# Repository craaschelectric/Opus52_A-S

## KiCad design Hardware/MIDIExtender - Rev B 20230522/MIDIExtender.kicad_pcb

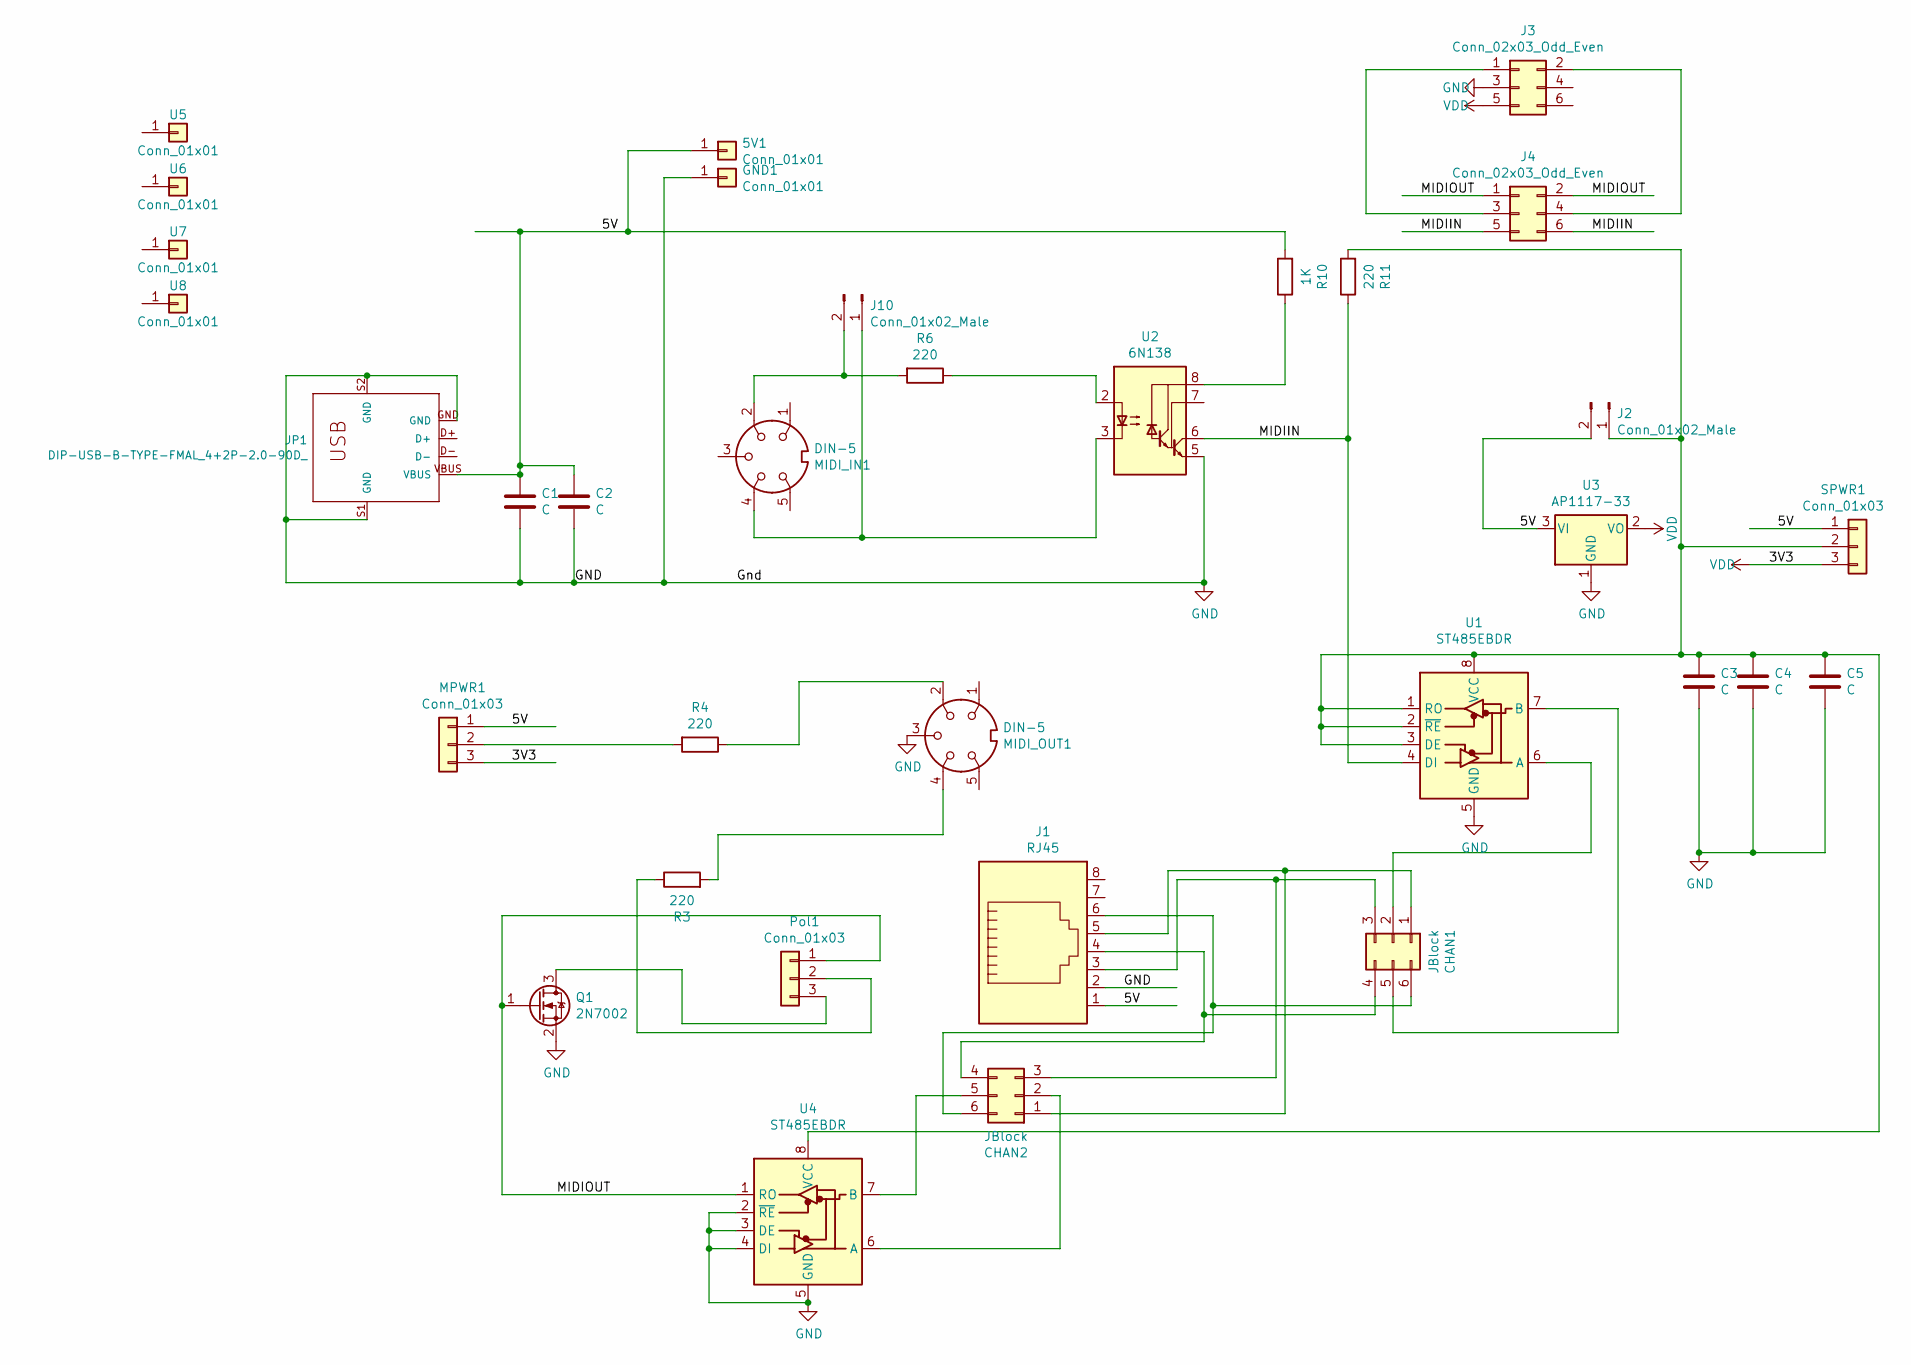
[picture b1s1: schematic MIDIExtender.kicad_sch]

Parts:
5V1: Conn_01x01; KK156-1
C1, C2, C3, C4, C5: C; C_0805_2012Metric_Pad1.15x1.40mm_HandSolder
CHAN1, CHAN2: JBlock; H2X3-2.54
GND1: Conn_01x01; KK156-1
J1: RJ45; RJ45_Amphenol_54602-x08_Horizontal
J2, J10: Conn_01x02_Male; H2-2.54
J3: Conn_02x03_Odd_Even; RibbonCableSocket_6_OddEven
J4: Conn_02x03_Odd_Even; PinHeader_2x03_P2.54mm_Vertical
JP1: DIP-USB-B-TYPE-FMAL_4+2P-2.0-90D_; USB4+2-2.5-90D-15.8X12MM
MIDI_IN1: DIN-5; DIN5_KCDX-5S-S2
MIDI_OUT1: DIN-5; DIN5_KCDX-5S-S2
MPWR1: Conn_01x03; H3-2.54
Pol1: Conn_01x03; H3-2.54
Q1: 2N7002; SOT-23
R3, R4, R6, R11: 220; R_0805_HandSoldering
R10: 1K; R_0805_HandSoldering
SPWR1: Conn_01x03; H3-2.54
U1, U4: ST485EBDR; SOIC-8_3.9x4.9mm_P1.27mm
U2: 6N138; DIP-8_W7.62mm
U3: AP1117-33; SOT-223-3_TabPin2
U5, U7, U8: Conn_01x01; Mounting#4
U6: Conn_01x01; SOT-223-3_TabPin2

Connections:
/5V: 5V1.1, C1.1, C2.1, J1.1, J2.2, JP1.VBUS, MPWR1.1, R10.2, SPWR1.1, U3.3 (VI)
/MIDIIN: J4.5, J4.6, R11.1, U1.4 (DI), U2.6 (VO2)
/MIDIOUT: J4.1, J4.2, Pol1.1, Q1.1 (G), U4.1 (RO)
GND: C1.2, C2.2, C3.2, C4.2, C5.2, GND1.1, J1.2, J3.3, JP1.GND, JP1.S1 (GND), JP1.S2 (GND), MIDI_OUT1.3, Q1.2 (S), U1.5 (GND), U2.5 (GND), U3.1 (GND), U4.2 (~RE), U4.3 (DE), U4.4 (DI), U4.5 (GND)
unnamed: C3.1, C4.1, C5.1, J2.1, R11.2, SPWR1.2, U1.1 (RO), U1.2 (~RE), U1.3 (DE), U1.8 (VCC), U4.8 (VCC)
unnamed: CHAN1.1, CHAN2.1, J1.5
unnamed: CHAN1.2, U1.6 (A)
unnamed: CHAN1.3, CHAN2.3, J1.3
unnamed: CHAN1.4, CHAN2.4, J1.4
unnamed: CHAN1.5, U1.7 (B)
unnamed: CHAN1.6, CHAN2.6, J1.6
unnamed: CHAN2.2, U4.6 (A)
unnamed: CHAN2.5, U4.7 (B)
unnamed: J3.1, J4.3
unnamed: J3.2, J4.4
unnamed: J10.1, MIDI_IN1.4, U2.3 (C2)
unnamed: J10.2, MIDI_IN1.2, R6.2
unnamed: MIDI_OUT1.2, R4.1
unnamed: MIDI_OUT1.4, R3.2
unnamed: MPWR1.2, R4.2
unnamed: Pol1.2, R3.1
unnamed: Pol1.3, Q1.3 (D)
unnamed: R6.1, U2.2 (C1)
unnamed: R10.1, U2.8 (VCC)
VDD: J3.5, MPWR1.3, SPWR1.3, U3.2 (VO)

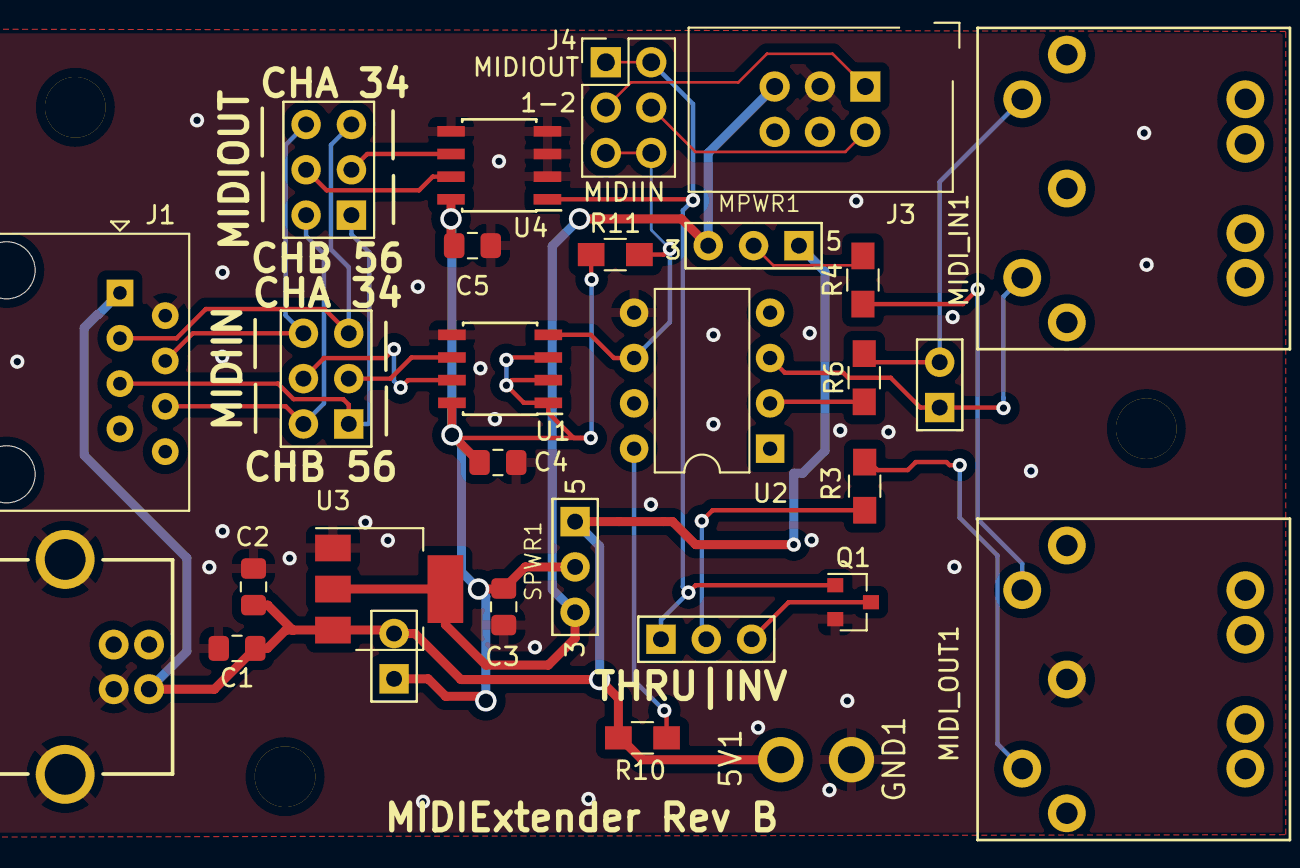
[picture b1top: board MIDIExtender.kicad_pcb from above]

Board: 2 copper layers, 33 parts (0 on the bottom side), 25 nets.

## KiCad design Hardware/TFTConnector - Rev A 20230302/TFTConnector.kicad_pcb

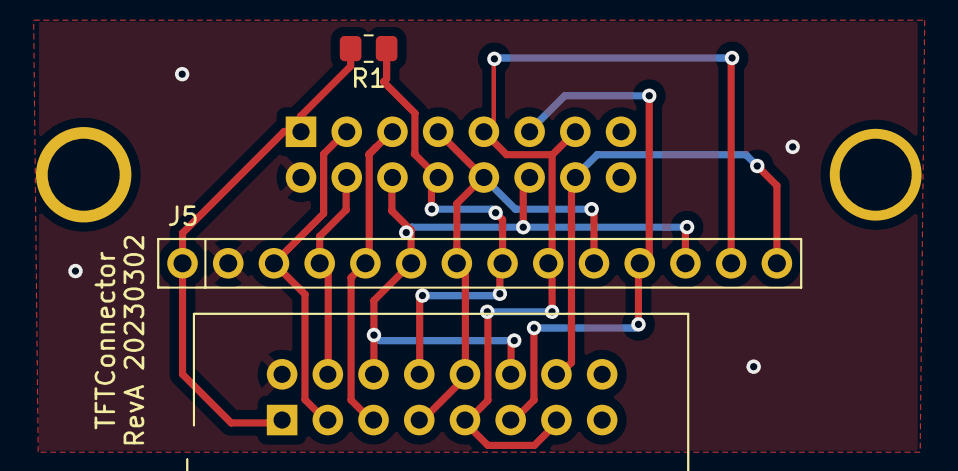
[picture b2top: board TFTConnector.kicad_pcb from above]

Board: 2 copper layers, 4 parts (1 on the bottom side), 11 nets.

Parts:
J5: Conn_01x14; PJRCTFT
J9, J12: Conn_02x08_Odd_Even; RibbonCableSocket_16_OddEven
R1: R; R_0805_2012Metric_Pad1.20x1.40mm_HandSolder

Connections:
/DC: J5.5, J9.5, J12.5
/GND: J5.2, J9.2, J12.2
/LEDBL: J5.8, J9.8, J12.8, R1.1
/SCK: J5.7, J5.10, J9.7, J9.10, J12.7, J12.10
/SDI_MOSI: J5.6, J5.12, J9.6, J9.12, J12.6, J12.12
/SDO_MISO: J5.9, J5.13, J9.9, J9.13, J12.9, J12.13
/TFT_CS: J5.3, J9.3, J12.3
/TFT_RST: J5.4, J9.4, J12.4
/Touch_CS: J5.11, J9.11, J12.11
/Touch_IRQ: J5.14, J9.14, J12.14
/VIN: J5.1, J9.1, J12.1, R1.2

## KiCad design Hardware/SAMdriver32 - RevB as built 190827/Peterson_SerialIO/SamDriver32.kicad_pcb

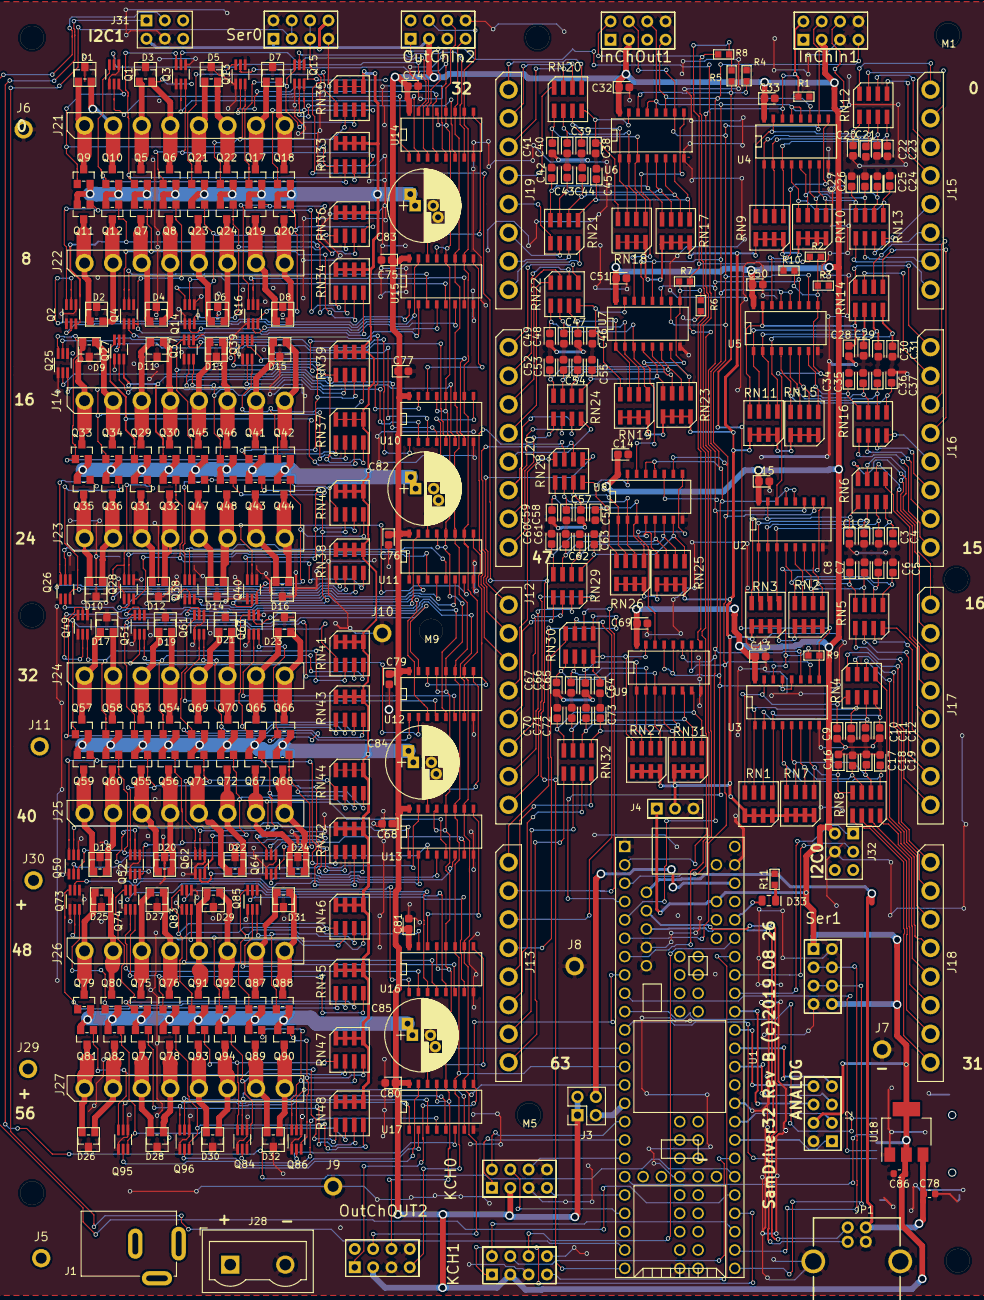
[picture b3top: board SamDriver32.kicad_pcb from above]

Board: 2 copper layers, 343 parts (1 on the bottom side), 384 nets.

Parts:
C1, C2, C3, C4, C5, C6, C7, C8, C9, C10, C11, C12, C16, C17, C18, C19, C20, C21, C22, C23, C24, C25, C26, C27, C28, C29, C30, C31, C34, C35, C36, C37, C38, C39, C40, C41, C42, C43, C44, C45, C46, C47, C48, C49, C52, C53, C54, C55, C56, C57, C58, C59, C60, C61, C62, C63, C64, C65, C66, C67, C70, C71, C72, C73: 1nf 302010138 or ESD; CP_EIA-1608-08_AVX-J
C13, C14, C15, C32, C33, C50, C51, C68, C69, C74, C75, C76, C77, C79, C80, C81: 302010138; CP_EIA-1608-08_AVX-J
C78, C86: CERAMIC-100NF-50V-10%-X7R_0603_; C_0603_1608Metric
C82, C83, C84, C85: 100uF 25V; CP_Radial_D10.0mm_P2.50mm_P5.00mm
D1, D2, D3, D4, D5, D6, D7, D8, D9, D10, D11, D12, D13, D14, D15, D16, D17, D18, D19, D20, D21, D22, D23, D24, D25, D26, D27, D28, D29, D30, D31, D32: BAV23A/Q; SOT-23
D33: SMD-LED-CLEAR-GREEN_0805_; R_0805_2012Metric
InChIn1: Conn_02x04_Counter_Clockwise; H2X4-2.54
InChOut1: Conn_02x04_Counter_Clockwise; H2X4-2.54
J1: JACK-DC-005; DCJ3P-14.2X11.0X9.0MM
J2: Conn_02x04_Counter_Clockwise; H2X4-2.54
J3: DIP-BLACK-MALE-HEADER-VERT_4P-2.54_; PinSocket_2x02_P2.54mm_Vertical
J4: Conn_01x03; H3-2.54
J5, J6, J7, J8, J9, J10, J11, J29, J30: Conn_01x01; KK156-1
J12, J13, J14, J15, J16, J17, J18, J19, J20, J21, J22, J23, J24, J25, J26, J27: Conn_01x08_Male; KK156-8
J28: Conn_01x02_Female; TerminalBlock_Wuerth_691311400102_P7.62mm
J31, J32: DIP-BLACK-MALE-HEADER_2X3P-2.54); H2X3-2.54
JP1: DIP-USB-B-TYPE-FMAL_4+2P-2.0-90D_; USB4+2-2.5-90D-15.8X12MM
KCH0, KCH1: Conn_02x04_Counter_Clockwise; H2X4-2.54
M1, M2, M3, M4, M5, M6, M7, M9, M10: Conn_01x01; Mounting#4
OutChIn2: Conn_02x04_Counter_Clockwise; H2X4-2.54
OutChOUT2: Conn_02x04_Counter_Clockwise; H2X4-2.54
Q1, Q2, Q3, Q4, Q13, Q14, Q15, Q16, Q25, Q26, Q27, Q28, Q37, Q38, Q39, Q40, Q49, Q50, Q51, Q52, Q61, Q62, Q63, Q64, Q73, Q74, Q83, Q84, Q85, Q86, Q95, Q96: 2N7002DW-7-F; SOT-363_SC-70-6_Handsoldering
Q5, Q6, Q7, Q8, Q9, Q10, Q11, Q12, Q17, Q18, Q19, Q20, Q21, Q22, Q23, Q24, Q29, Q30, Q31, Q32, Q33, Q34, Q35, Q36, Q41, Q42, Q43, Q44, Q45, Q46, Q47, Q48, Q53, Q54, Q55, Q56, Q57, Q58, Q59, Q60, Q65, Q66, Q67, Q68, Q69, Q70, Q71, Q72, Q75, Q76, Q77, Q78, Q79, Q80, Q81, Q82, Q87, Q88, Q89, Q90, Q91, Q92, Q93, Q94: SMD-MOSFET-P-CH-VDC=30V-ID=4.3A-NCE3407A_SOT-23_; SOT-23
R1, R2, R3, R4, R5, R6, R7, R8, R11: DNP; R0603
R9, R10: R; R0603
RN1, RN2, RN3, RN4, RN5, RN6, RN7, RN8, RN9, RN10, RN11, RN12, RN13, RN14, RN15, RN16, RN17, RN18, RN19, RN20, RN21, RN22, RN23, RN24, RN25, RN26, RN27, RN28, RN29, RN30, RN31, RN32, RN33, RN34, RN35, RN36, RN37, RN38, RN39, RN40, RN41, RN42, RN43, RN44, RN45, RN46, RN47, RN48: R_Pack04; 2012-8
SD1: MICRO-SD-CARD-SOCKET-9P_ST-TF-003A_; MICRO-SD9+4P-SMD-16.1X14.5X1.85MM
Ser0, Ser1: Conn_02x04_Counter_Clockwise; H2X4-2.54
U1: Teensy3.6; Teensy35_36
U2, U3, U4, U5, U6, U7, U8, U9: 74HC597; SO-16-N
U10, U11, U12, U13, U14, U15, U16, U17: 74HC595D,118; SO-16-N
U18: AP1117-33; SOT-223-3_TabPin2

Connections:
/DMINUS: JP1.D-, U1.59
/DPLUS: JP1.D+, U1.60
/INSENSE: R2.2, R5.2, R7.2, R8.2, U1.3
/InChainIn: InChIn1.8, R1.1, U1.2, U4.14
/InChainOut: InChOut1.8, R8.1, U9.9
/InRegLoad: InChIn1.6, InChOut1.6, U1.4, U2.12, U2.13, U3.12, U3.13, U4.12, U4.13, U5.12, U5.13, U6.12, U6.13, U7.12, U7.13, U8.12, U8.13, U9.12, U9.13
/KCH0CLK: KCH0.4, U1.20
/KCH0IN: KCH0.1, U1.17
/KCH0LOAD: KCH0.6, U1.18
/KCH0OUT: KCH0.8, U1.16
/KCH0RST: KCH0.7, U1.21
/KCH1CLK: KCH1.4, U1.47
/KCH1IN: KCH1.1, U1.33
/KCH1LOAD: KCH1.6, U1.48
/KCH1OUT: KCH1.8, U1.32
/KCH1RST: KCH1.7, U1.36
/MISO: SD1.7, U1.10
/MOSI: SD1.3, U1.9
/OUT16: J17.1, RN6.8
/OUT17: J17.2, RN6.7
/OUT18: J17.3, RN6.6
/OUT19: J17.4, RN6.5
/OUT20: J17.5, RN5.8
/OUT21: J17.6, RN5.7
/OUT22: J17.7, RN5.6
/OUT23: J17.8, RN5.5
/OUT24: J18.1, RN4.8
/OUT25: J18.2, RN4.7
/OUT26: J18.3, RN4.6
/OUT27: J18.4, RN4.5
/OUT28: J18.5, RN8.8
/OUT29: J18.6, RN8.7
/OUT30: J18.7, RN8.6
/OUT31: J18.8, RN8.5
/OUT32: J19.1, RN20.5
/OUT33: J19.2, RN20.6
/OUT34: J19.3, RN20.7
/OUT35: J19.4, RN20.8
/OUT36: J19.5, RN21.5
/OUT37: J19.6, RN21.6
/OUT38: J19.7, RN21.7
/OUT39: J19.8, RN21.8
/OUT40: J20.1, RN22.5
/OUT41: J20.2, RN22.6
/OUT42: J20.3, RN22.7
/OUT43: J20.4, RN22.8
/OUT44: J20.5, RN24.8
/OUT45: J20.6, RN24.7
/OUT46: J20.7, RN24.6
/OUT47: J20.8, RN24.5
/OUT48: J12.1, RN28.5
/OUT49: J12.2, RN28.6
/OUT50: J12.3, RN28.7
/OUT51: J12.4, RN28.8
/OUT52: J12.5, RN29.5
/OUT53: J12.6, RN29.6
/OUT54: J12.7, RN29.7
/OUT55: J12.8, RN29.8
/OUT56: J13.1, RN30.5
/OUT57: J13.2, RN30.6
/OUT58: J13.3, RN30.7
/OUT59: J13.4, RN30.8
/OUT60: J13.5, RN32.8
/OUT61: J13.6, RN32.7
/OUT62: J13.7, RN32.6
/OUT63: J13.8, RN32.5
/Out0_15/DRVA00: Q1.2, U14.15
/Out0_15/DRVA01: Q1.5, U14.1
/Out0_15/DRVA02: Q3.2, U14.2
/Out0_15/DRVA03: Q3.5, U14.3
/Out0_15/DRVA04: Q13.2, U14.4
/Out0_15/DRVA05: Q13.5, U14.5
/Out0_15/DRVA06: Q15.2, U14.6
/Out0_15/DRVA07: Q15.5, U14.7
/Out0_15/DRVA08: Q2.2, U15.15
/Out0_15/DRVA09: Q2.5, U15.1
/Out0_15/DRVA10: Q4.2, U15.2
/Out0_15/DRVA11: Q4.5, U15.3
/Out0_15/DRVA12: Q14.2, U15.4
/Out0_15/DRVA13: Q14.5, U15.5
/Out0_15/DRVA14: Q16.2, U15.6
/Out0_15/DRVA15: Q16.5, U15.7
/Out0_15/SAMA00: D1.1, J21.1, Q9.3
/Out0_15/SAMA01: D1.2, J21.2, Q10.3
/Out0_15/SAMA02: D3.1, J21.3, Q5.3
/Out0_15/SAMA03: D3.2, J21.4, Q6.3
/Out0_15/SAMA04: D5.1, J21.5, Q21.3
/Out0_15/SAMA05: D5.2, J21.6, Q22.3
/Out0_15/SAMA06: D7.1, J21.7, Q17.3
/Out0_15/SAMA07: D7.2, J21.8, Q18.3
/Out0_15/SAMA08: D2.1, J22.1, Q11.3
/Out0_15/SAMA09: D2.2, J22.2, Q12.3
/Outputs 32_47/DRVC00: Q49.2, U12.15
/Outputs 32_47/DRVC01: Q49.5, U12.1
/Outputs 32_47/DRVC02: Q51.2, U12.2
/Outputs 32_47/DRVC03: Q51.5, U12.3
/Outputs 32_47/DRVC04: Q61.2, U12.4
/Outputs 32_47/DRVC05: Q61.5, U12.5
/Outputs 32_47/DRVC06: Q63.2, U12.6
/Outputs 32_47/DRVC07: Q63.5, U12.7
/Outputs 32_47/DRVC08: Q50.2, U13.15
/Outputs 32_47/DRVC09: Q50.5, U13.1
/Outputs 32_47/DRVC10: Q52.2, U13.2
/Outputs 32_47/DRVC11: Q52.5, U13.3
/Outputs 32_47/DRVC12: Q62.2, U13.4
/Outputs 32_47/DRVC13: Q62.5, U13.5
/Outputs 32_47/DRVC14: Q64.2, U13.6
/Outputs 32_47/DRVC15: Q64.5, U13.7
/Outputs 32_47/SAMC00: D17.1, J24.1, Q57.3
/Outputs 32_47/SAMC01: D17.2, J24.2, Q58.3
/Outputs 32_47/SAMC02: D19.1, J24.3, Q53.3
/Outputs 32_47/SAMC03: D19.2, J24.4, Q54.3
/Outputs 32_47/SAMC04: D21.1, J24.5, Q69.3
/Outputs 32_47/SAMC05: D21.2, J24.6, Q70.3
/Outputs 32_47/SAMC06: D23.1, J24.7, Q65.3
/Outputs 32_47/SAMC07: D23.2, J24.8, Q66.3
/Outputs 32_47/SAMC08: D18.1, J25.1, Q59.3
/Outputs 32_47/SAMC09: D18.2, J25.2, Q60.3
/Outputs 48_63/DRVD00: Q73.2, U16.15
/Outputs 48_63/DRVD01: Q73.5, U16.1
/Outputs 48_63/DRVD02: Q74.2, U16.2
/Outputs 48_63/DRVD03: Q74.5, U16.3
/Outputs 48_63/DRVD04: Q83.2, U16.4
/Outputs 48_63/DRVD05: Q83.5, U16.5
/Outputs 48_63/DRVD06: Q85.2, U16.6
/Outputs 48_63/DRVD07: Q85.5, U16.7
/Outputs 48_63/DRVD08: Q95.2, U17.15
/Outputs 48_63/DRVD09: Q95.5, U17.1
/Outputs 48_63/DRVD10: Q96.2, U17.2
/Outputs 48_63/DRVD11: Q96.5, U17.3
/Outputs 48_63/DRVD12: Q84.2, U17.4
/Outputs 48_63/DRVD13: Q84.5, U17.5
/Outputs 48_63/DRVD14: Q86.2, U17.6
/Outputs 48_63/DRVD15: Q86.5, U17.7
/Outputs 48_63/SAMD00: D25.2, J26.1, Q79.3
/Outputs 48_63/SAMD01: D25.1, J26.2, Q80.3
/Outputs 48_63/SAMD02: D27.2, J26.3, Q75.3
/Outputs 48_63/SAMD03: D27.1, J26.4, Q76.3
/Outputs 48_63/SAMD04: D29.2, J26.5, Q91.3
/Outputs 48_63/SAMD05: D29.1, J26.6, Q92.3
/Outputs 48_63/SAMD06: D31.2, J26.7, Q87.3
/Outputs 48_63/SAMD07: D31.1, J26.8, Q88.3
/Outputs 48_63/SAMD08: D26.2, J27.1, Q81.3
/Outputs 48_63/SAMD09: D26.1, J27.2, Q82.3
/PULLTERM: J4.2, RN1.5, RN1.6, RN1.7, RN1.8, RN2.5, RN2.6, RN2.7, RN2.8, RN3.5, RN3.6, RN3.7, RN3.8, RN7.5, RN7.6, RN7.7, RN7.8, RN9.5, RN9.6, RN9.7, RN9.8, RN10.5, RN10.6, RN10.7, RN10.8, RN11.5, RN11.6, RN11.7, RN11.8, RN15.5, RN15.6, RN15.7, RN15.8, RN17.5, RN17.6, RN17.7, RN17.8, RN18.5, RN18.6, RN18.7, RN18.8, RN19.5, RN19.6, RN19.7, RN19.8, RN23.5, RN23.6, RN23.7, RN23.8, RN25.5, RN25.6, RN25.7, RN25.8, RN26.5, RN26.6, RN26.7, RN26.8, RN27.5, RN27.6, RN27.7, RN27.8, RN31.5, RN31.6, RN31.7, RN31.8
/Ports16_32/SERIn1: R2.1, R3.2, R10.1, U2.14, U5.9
/Ports33_48/SERIn2: R4.2, R5.1, R9.1, U3.9, U6.14
/Ports49_64/SERIn3: R6.1, R7.1, U7.9, U8.14
/RX4: Ser0.2, Ser0.7, U1.23
/RX5_SDA0: Ser1.2, Ser1.7, U1.31
/SCK: SD1.5, U1.19
/SCL0: J32.2, U1.46
/SCL1: J31.2, U1.34
/SDA0: J32.1, U1.45
/SDA1: J31.1, U1.35
/SDCS: SD1.2, U1.11
/TX4: Ser0.3, Ser0.6, U1.24
/TX5_SCL0: Ser1.3, Ser1.6, U1.30
/VBUS: C78.1, JP1.VBUS, U1.58, U18.3
/nRST: InChIn1.7, InChOut1.7, U1.6, U2.10, U3.10, U4.10, U5.10, U6.10, U7.10, U8.10, U9.10
/sheet5D08CCA3/DRVB00: Q25.2, U10.15
/sheet5D08CCA3/DRVB01: Q25.5, U10.1
/sheet5D08CCA3/DRVB02: Q27.2, U10.2
/sheet5D08CCA3/DRVB03: Q27.5, U10.3
/sheet5D08CCA3/DRVB04: Q37.2, U10.4
/sheet5D08CCA3/DRVB05: Q37.5, U10.5
/sheet5D08CCA3/DRVB06: Q39.2, U10.6
/sheet5D08CCA3/DRVB07: Q39.5, U10.7
/sheet5D08CCA3/DRVB08: Q26.2, U11.15
/sheet5D08CCA3/DRVB09: Q26.5, U11.1
/sheet5D08CCA3/DRVB10: Q28.2, U11.2
/sheet5D08CCA3/DRVB11: Q28.5, U11.3
/sheet5D08CCA3/DRVB12: Q38.2, U11.4
/sheet5D08CCA3/DRVB13: Q38.5, U11.5
/sheet5D08CCA3/DRVB14: Q40.2, U11.6
/sheet5D08CCA3/DRVB15: Q40.5, U11.7
/sheet5D08CCA3/SAMB00: D9.2, J14.1, Q33.3
/sheet5D08CCA3/SAMB01: D9.1, J14.2, Q34.3
/sheet5D08CCA3/SAMB02: D11.2, J14.3, Q29.3
/sheet5D08CCA3/SAMB03: D11.1, J14.4, Q30.3
/sheet5D08CCA3/SAMB04: D13.2, J14.5, Q45.3
/sheet5D08CCA3/SAMB05: D13.1, J14.6, Q46.3
/sheet5D08CCA3/SAMB06: D15.2, J14.7, Q41.3
/sheet5D08CCA3/SAMB07: D15.1, J14.8, Q42.3
/sheet5D08CCA3/SAMB08: D10.2, J23.1, Q35.3
/sheet5D08CCA3/SAMB09: D10.1, J23.2, Q36.3
GND: C1.2, C2.2, C3.2, C4.2, C5.2, C6.2, C7.2, C8.2, C9.2, C10.2, C11.2, C12.2, C13.2, C14.2, C15.2, C16.2, C17.2, C18.2, C19.2, C20.2, C21.2, C22.2, C23.2, C24.2, C25.2, C26.2, C27.2, C28.2, C29.2, C30.2, C31.2, C32.2, C33.2, C34.2, C35.2, C36.2, C37.2, C38.2, C39.2, C40.2, C41.2, C42.2, C43.2, C44.2, C45.2, C46.2, C47.2, C48.2, C49.2, C50.2, C51.2, C52.2, C53.2, C54.2, C55.2, C56.2, C57.2, C58.2, C59.2, C60.2, C61.2, C62.2, C63.2, C64.2, C65.2, C66.2, C67.2, C68.2, C69.2, C70.2, C71.2, C72.2, C73.2, C74.2, C75.2, C76.2, C77.2, C78.2, C79.2, C80.2, C81.2, C82.2, C83.2, C84.2, C85.2, C86.2, D1.3, D2.3, D3.3, D4.3, D5.3, D6.3, D7.3, D8.3, D9.3, D10.3, D11.3, D12.3, D13.3, D14.3, D15.3, D16.3, D17.3, D18.3, D19.3, D20.3, D21.3, D22.3, D23.3, D24.3, D25.3, D26.3, D27.3, D28.3, D29.3, D30.3, D31.3, D32.3, InChIn1.3, InChIn1.5, InChOut1.3, InChOut1.5, J2.8, J4.3, J6.1, J7.1, J8.1, J9.1, J10.1, J28.2, J31.5, J32.5, JP1.GND, JP1.S1, JP1.S2, KCH0.3, KCH0.5, KCH1.3, KCH1.5, OutChIn2.3, OutChIn2.5, OutChOUT2.3, OutChOUT2.5, Q1.1, Q1.4, Q2.1, Q2.4, Q3.1, Q3.4, Q4.1, Q4.4, Q13.1, Q13.4, Q14.1, Q14.4, Q15.1, Q15.4, Q16.1, Q16.4, Q25.1, Q25.4, Q26.1, Q26.4, Q27.1, Q27.4, Q28.1, Q28.4, Q37.1, Q37.4, Q38.1, Q38.4, Q39.1, Q39.4, Q40.1, Q40.4, Q49.1, Q49.4, Q50.1, Q50.4, Q51.1, Q51.4, Q52.1, Q52.4, Q61.1, Q61.4, Q62.1, Q62.4, Q63.1, Q63.4, Q64.1, Q64.4, Q73.1, Q73.4, Q74.1, Q74.4, Q83.1, Q83.4, Q84.1, Q84.4, Q85.1, Q85.4, Q86.1, Q86.4, Q95.1, Q95.4, Q96.1, Q96.4, R1.2, R3.1, R4.1, R6.2, R11.2, SD1.6, SD1.10, SD1.11, SD1.12, SD1.13, Ser0.4, Ser0.8, Ser1.4, Ser1.8, U1.1, U1.27, U1.39, U1.52, U1.61, U1.62, U1.74, U2.8, U3.8, U4.8, U5.8, U6.8, U7.8, U8.8, U9.8, U10.8, U11.8, U12.8, U13.8, U14.8, U15.8, U16.8, U17.8, U18.1
unnamed: C1.1, RN3.4, RN6.1, U2.15
unnamed: C2.1, RN3.3, RN6.2, U2.1
unnamed: C3.1, RN3.2, RN6.3, U2.2
unnamed: C4.1, RN3.1, RN6.4, U2.3
unnamed: C5.1, RN2.4, RN5.1, U2.4
unnamed: C6.1, RN2.3, RN5.2, U2.5
unnamed: C7.1, RN2.2, RN5.3, U2.6
unnamed: C8.1, RN2.1, RN5.4, U2.7
unnamed: C9.1, RN1.4, RN4.1, U3.15
unnamed: C10.1, RN1.3, RN4.2, U3.1
unnamed: C11.1, RN1.2, RN4.3, U3.2
unnamed: C12.1, RN1.1, RN4.4, U3.3
unnamed: C16.1, RN7.1, RN8.4, U3.7
unnamed: C17.1, RN7.2, RN8.3, U3.6
unnamed: C18.1, RN7.3, RN8.2, U3.5
unnamed: C19.1, RN7.4, RN8.1, U3.4
unnamed: C20.1, RN9.4, RN12.1, U4.15
unnamed: C21.1, RN9.3, RN12.2, U4.1
unnamed: C22.1, RN9.2, RN12.3, U4.2
unnamed: C23.1, RN9.1, RN12.4, U4.3
unnamed: C24.1, RN10.4, RN13.1, U4.4
unnamed: C25.1, RN10.3, RN13.2, U4.5
unnamed: C26.1, RN10.2, RN13.3, U4.6
unnamed: C27.1, RN10.1, RN13.4, U4.7
unnamed: C28.1, RN11.4, RN14.1, U5.15
unnamed: C29.1, RN11.3, RN14.2, U5.1
unnamed: C30.1, RN11.2, RN14.3, U5.2
unnamed: C31.1, RN11.1, RN14.4, U5.3
unnamed: C34.1, RN15.1, RN16.4, U5.7
unnamed: C35.1, RN15.2, RN16.3, U5.6
unnamed: C36.1, RN15.3, RN16.2, U5.5
unnamed: C37.1, RN15.4, RN16.1, U5.4
unnamed: C38.1, RN18.4, RN20.4, U6.15
unnamed: C39.1, RN18.3, RN20.3, U6.1
unnamed: C40.1, RN18.2, RN20.2, U6.2
unnamed: C41.1, RN18.1, RN20.1, U6.3
unnamed: C42.1, RN17.4, RN21.4, U6.4
unnamed: C43.1, RN17.3, RN21.3, U6.5
unnamed: C44.1, RN17.2, RN21.2, U6.6
unnamed: C45.1, RN17.1, RN21.1, U6.7
unnamed: C46.1, RN19.4, RN22.4, U7.15
unnamed: C47.1, RN19.3, RN22.3, U7.1
unnamed: C48.1, RN19.2, RN22.2, U7.2
unnamed: C49.1, RN19.1, RN22.1, U7.3
unnamed: C52.1, RN23.1, RN24.4, U7.7
unnamed: C53.1, RN23.2, RN24.3, U7.6
unnamed: C54.1, RN23.3, RN24.2, U7.5
unnamed: C55.1, RN23.4, RN24.1, U7.4
unnamed: C56.1, RN26.4, RN28.4, U8.15
unnamed: C57.1, RN26.3, RN28.3, U8.1
unnamed: C58.1, RN26.2, RN28.2, U8.2
unnamed: C59.1, RN26.1, RN28.1, U8.3
unnamed: C60.1, RN25.4, RN29.4, U8.4
unnamed: C61.1, RN25.3, RN29.3, U8.5
unnamed: C62.1, RN25.2, RN29.2, U8.6
unnamed: C63.1, RN25.1, RN29.1, U8.7
unnamed: C64.1, RN27.4, RN30.4, U9.15
unnamed: C65.1, RN27.3, RN30.3, U9.1
unnamed: C66.1, RN27.2, RN30.2, U9.2
unnamed: C67.1, RN27.1, RN30.1, U9.3
unnamed: C70.1, RN31.1, RN32.4, U9.7
unnamed: C71.1, RN31.2, RN32.3, U9.6
unnamed: C72.1, RN31.3, RN32.2, U9.5
unnamed: C73.1, RN31.4, RN32.1, U9.4
unnamed: D33.1, U1.49
unnamed: D33.2, R11.1
unnamed: J2.1, U1.37
unnamed: J2.2, U1.38
unnamed: J2.3, U1.41
unnamed: J2.4, U1.42
unnamed: J2.5, U1.43
unnamed: J2.6, U1.44
unnamed: J3.2, U1.15
unnamed: J3.4, U1.51
unnamed: Q1.3, Q10.1, RN33.2
unnamed: Q1.6, Q9.1, RN33.1
unnamed: Q3.3, Q6.1, RN33.4
unnamed: Q3.6, Q5.1, RN33.3
unnamed: Q4.3, Q8.1, RN34.4
unnamed: Q4.6, Q7.1, RN34.3
unnamed: Q2.6, Q11.1, RN34.1
unnamed: Q2.3, Q12.1, RN34.2
unnamed: Q13.3, Q22.1, RN35.2
unnamed: Q13.6, Q21.1, RN35.1
unnamed: Q14.3, Q24.1, RN36.2
unnamed: Q14.6, Q23.1, RN36.1
unnamed: Q15.3, Q18.1, RN35.4
unnamed: Q15.6, Q17.1, RN35.3
unnamed: Q16.3, Q20.1, RN36.4
unnamed: Q16.6, Q19.1, RN36.3
unnamed: Q25.3, Q34.1, RN37.2
unnamed: Q25.6, Q33.1, RN37.1
unnamed: Q26.3, Q36.1, RN38.2
unnamed: Q26.6, Q35.1, RN38.1
unnamed: Q27.3, Q30.1, RN37.4
unnamed: Q27.6, Q29.1, RN37.3
unnamed: Q28.3, Q32.1, RN38.4
unnamed: Q28.6, Q31.1, RN38.3
unnamed: Q37.3, Q46.1, RN39.2
unnamed: Q37.6, Q45.1, RN39.1
unnamed: Q38.3, Q48.1, RN40.2
unnamed: Q38.6, Q47.1, RN40.1
unnamed: Q39.3, Q42.1, RN39.4
unnamed: Q39.6, Q41.1, RN39.3
unnamed: Q40.3, Q44.1, RN40.4
unnamed: Q40.6, Q43.1, RN40.3
unnamed: Q49.3, Q58.1, RN41.2
unnamed: Q49.6, Q57.1, RN41.1
unnamed: Q50.3, Q60.1, RN42.2
unnamed: Q50.6, Q59.1, RN42.1
unnamed: Q51.3, Q54.1, RN41.4
unnamed: Q51.6, Q53.1, RN41.3
unnamed: Q52.3, Q56.1, RN42.4
unnamed: Q52.6, Q55.1, RN42.3
unnamed: Q61.3, Q70.1, RN43.2
unnamed: Q61.6, Q69.1, RN43.1
unnamed: Q62.3, Q72.1, RN44.2
unnamed: Q62.6, Q71.1, RN44.1
unnamed: Q63.3, Q66.1, RN43.4
unnamed: Q63.6, Q65.1, RN43.3
unnamed: Q64.3, Q68.1, RN44.4
unnamed: Q64.6, Q67.1, RN44.3
unnamed: Q73.3, Q80.1, RN45.2
unnamed: Q73.6, Q79.1, RN45.1
unnamed: Q74.3, Q76.1, RN45.4
unnamed: Q74.6, Q75.1, RN45.3
unnamed: Q77.1, Q96.6, RN48.3
unnamed: Q78.1, Q96.3, RN48.4
unnamed: Q81.1, Q95.6, RN48.1
unnamed: Q82.1, Q95.3, RN48.2
unnamed: Q83.3, Q92.1, RN46.2
unnamed: Q83.6, Q91.1, RN46.1
unnamed: Q84.3, Q94.1, RN47.2
unnamed: Q84.6, Q93.1, RN47.1
unnamed: Q85.3, Q88.1, RN46.4
unnamed: Q85.6, Q87.1, RN46.3
unnamed: Q86.3, Q90.1, RN47.4
unnamed: Q86.6, Q89.1, RN47.3
unnamed: R9.2, U2.9, U3.14
unnamed: R10.2, U4.9, U5.14
unnamed: U6.9, U7.14
unnamed: U8.9, U9.14
unnamed: U10.9, U11.14
unnamed: U12.9, U13.14
unnamed: U14.9, U15.14
unnamed: U16.9, U17.14
OUT0: J15.1, RN12.8
OUT1: J15.2, RN12.7
OUT2: J15.3, RN12.6
OUT3: J15.4, RN12.5
OUT4: J15.5, RN13.8
OUT5: J15.6, RN13.7
OUT6: J15.7, RN13.6
OUT7: J15.8, RN13.5
OUT8: J16.1, RN14.8
OUT9: J16.2, RN14.7
OUT10: J16.3, RN14.6
OUT11: J16.4, RN14.5
OUT12: J16.5, RN16.8
OUT13: J16.6, RN16.7
OUT14: J16.7, RN16.6
OUT15: J16.8, RN16.5
OutRST: OutChIn2.7, OutChOUT2.7, U1.14, U10.10, U11.10, U12.10, U13.10, U14.10, U15.10, U16.10, U17.10
OutRegLoad: OutChIn2.6, OutChOUT2.6, U1.12, U10.12, U10.13, U11.12, U11.13, U12.12, U12.13, U13.12, U13.13, U14.12, U14.13, U15.12, U15.13, U16.12, U16.13, U17.12, U17.13
OutSerCK: OutChIn2.4, OutChOUT2.4, U1.13, U10.11, U11.11, U12.11, U13.11, U14.11, U15.11, U16.11, U17.11
SAMA10: D4.1, J22.3, Q7.3
SAMA11: D4.2, J22.4, Q8.3
SAMA12: D6.1, J22.5, Q23.3
SAMA13: D6.2, J22.6, Q24.3
SAMA14: D8.1, J22.7, Q19.3
SAMA15: D8.2, J22.8, Q20.3
SAMAX: U10.14, U15.9
SAMB10: D12.2, J23.3, Q31.3
SAMB11: D12.1, J23.4, Q32.3
SAMB12: D14.2, J23.5, Q47.3
SAMB13: D14.1, J23.6, Q48.3
SAMB14: D16.2, J23.7, Q43.3
SAMB15: D16.1, J23.8, Q44.3
SAMBX: U11.9, U12.14
SAMC10: D20.1, J25.3, Q55.3
SAMC11: D20.2, J25.4, Q56.3
SAMC12: D22.1, J25.5, Q71.3
SAMC13: D22.2, J25.6, Q72.3
SAMC14: D24.1, J25.7, Q67.3
SAMC15: D24.2, J25.8, Q68.3
SAMCX: U13.9, U16.14
SAMD10: D28.2, J27.3, Q77.3
SAMD11: D28.1, J27.4, Q78.3
SAMD12: D30.2, J27.5, Q93.3
SAMD13: D30.1, J27.6, Q94.3
SAMD14: D32.2, J27.7, Q89.3
SAMD15: D32.1, J27.8, Q90.3
SAMDX: OutChOUT2.1, U1.8, U17.9
SAMInput: OutChIn2.1, U1.7, U14.14
SAMPWR: C82.1, C83.1, C84.1, C85.1, J5.1, J11.1, J28.1, J29.1, J30.1, Q5.2, Q6.2, Q7.2, Q8.2, Q9.2, Q10.2, Q11.2, Q12.2, Q17.2, Q18.2, Q19.2, Q20.2, Q21.2, Q22.2, Q23.2, Q24.2, Q29.2, Q30.2, Q31.2, Q32.2, Q33.2, Q34.2, Q35.2, Q36.2, Q41.2, Q42.2, Q43.2, Q44.2, Q45.2, Q46.2, Q47.2, Q48.2, Q53.2, Q54.2, Q55.2, Q56.2, Q57.2, Q58.2, Q59.2, Q60.2, Q65.2, Q66.2, Q67.2, Q68.2, Q69.2, Q70.2, Q71.2, Q72.2, Q75.2, Q76.2, Q77.2, Q78.2, Q79.2, Q80.2, Q81.2, Q82.2, Q87.2, Q88.2, Q89.2, Q90.2, Q91.2, Q92.2, Q93.2, Q94.2, RN33.5, RN33.6, RN33.7, RN33.8, RN34.5, RN34.6, RN34.7, RN34.8, RN35.5, RN35.6, RN35.7, RN35.8, RN36.5, RN36.6, RN36.7, RN36.8, RN37.5, RN37.6, RN37.7, RN37.8, RN38.5, RN38.6, RN38.7, RN38.8, RN39.5, RN39.6, RN39.7, RN39.8, RN40.5, RN40.6, RN40.7, RN40.8, RN41.5, RN41.6, RN41.7, RN41.8, RN42.5, RN42.6, RN42.7, RN42.8, RN43.5, RN43.6, RN43.7, RN43.8, RN44.5, RN44.6, RN44.7, RN44.8, RN45.5, RN45.6, RN45.7, RN45.8, RN46.5, RN46.6, RN46.7, RN46.8, RN47.5, RN47.6, RN47.7, RN47.8, RN48.5, RN48.6, RN48.7, RN48.8
SerialCLK: InChIn1.4, InChOut1.4, U1.5, U2.11, U3.11, U4.11, U5.11, U6.11, U7.11, U8.11, U9.11
VCC: C13.1, C14.1, C15.1, C32.1, C33.1, C50.1, C51.1, C68.1, C69.1, C74.1, C75.1, C76.1, C77.1, C79.1, C80.1, C81.1, C86.1, InChIn1.2, InChOut1.2, J2.7, J3.1, J3.3, J4.1, J31.4, J32.4, KCH0.2, KCH1.2, OutChIn2.2, OutChOUT2.2, SD1.4, Ser0.1, Ser0.5, Ser1.1, Ser1.5, U1.55, U2.16, U3.16, U4.16, U5.16, U6.16, U7.16, U8.16, U9.16, U10.16, U11.16, U12.16, U13.16, U14.16, U15.16, U16.16, U17.16, U18.2

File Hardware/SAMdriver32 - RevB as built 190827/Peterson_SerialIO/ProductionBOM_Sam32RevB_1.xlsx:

Qty/board | Reference(s) | Value | LibPart | Footprint | STOCK | Notes | Qty ordered |  | Part Ordered
0 | C1, C2, C3, C4, C5, C6, C7, C8, C9, C10, C11, C12, C16, C17, C18, C19, C20, C21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 | 1nf 302010138 or ESD | Device:C | Capacitor_Tantalum_SMD:CP_EIA-1608-08_AVX-J |  | DNP
0 | J3 | DIP-BLACK-MALE-HEADER-VERT_4P-2.54_ | OPL_Connector:DIP-BLACK-MALE-HEADER-VERT_4P-2.54_ | Connector_PinSocket_2.54mm:PinSocket_2x02_P2.54mm_Vertical |  | DNP
0 | J5, J6, J7, J8, J9, J10, J11, J29, J30 | Conn_01x01 | SerialIOProc-rescue:Conn_01x01-conn | CLRConnector:KK156-1 |  | DNP
0 | M1, M2, M3, M4, M5, M6, M7, M9, M10 | Conn_01x01 | SerialIOProc-rescue:Conn_01x01-conn | CLRConnector:Mounting#4 |  | DNP
0 | R1, R2, R3, R4, R5, R6, R7, R8 | DNP | Device:R | SeeedOPL-Resistor-2016:R0603 |  | DNP
0 | R9, R10 | R | Device:R | SeeedOPL-Resistor-2016:R0603 |  | DNP
0 | R11 | DNP | Device:R | OPL_Resistor:R0603 |  | DNP
0 | U1 | Teensy3.6 | teensy:Teensy3.6 | CLRLibraryParts:Teensy35_36 |  | DNP
1 | J4 | Conn_01x03 | SerialIOProc-rescue:Conn_01x03-conn | CLRConnector:H3-2.54 |  | Short pins 1-2
4 | C82, C83, C84, C85 | 100uF 25V | Device:C_Small | Capacitors_THT:CP_Radial_D10.0mm_P2.50mm_P5.00mm |  | T/H | 20 | 20 | ESE477M025AH1EA
9 | InChIn1, InChOut1, J2, KCH0, KCH1, OutChIn2, OutChOUT2, Ser0, Ser1 | Conn_02x04_Counter_Clockwise | SerialIOProc-rescue:Conn_02x04_Counter_Clockwise-conn | SeeedOPL-Connector-2016:H2X4-2.54 | ?? | T/H - Use up stock
16 | J12, J13, J14, J15, J16, J17, J18, J19, J20, J21, J22, J23, J24, J25, J26, J27 | Conn_01x08_Male | Connector:Conn_01x08_Male | CLRLibraryParts:KK156-8 |  | T/H | 80 | 80 | 0026481081
1 | J28 | Conn_01x02_Female | Connector:Conn_01x02_Female | TerminalBlock:TerminalBlock_Wuerth_691311400102_P7.62mm |  | T/H | 5 | 5 | 1809898 - PHOENIX CONTACT
2 | J31, J32 | DIP-BLACK-MALE-HEADER_2X3P-2.54) | OPL_Connector:DIP-BLACK-MALE-HEADER_2X3P-2.54) | OPL_Connector:H2X3-2.54 |  | T/H | 10 | 10 | 75869-131LF
1 | JP1 | DIP-USB-B-TYPE-FMAL_4+2P-2.0-90D_ | SeeedOPL-Connector-2016:DIP-USB-B-TYPE-FMAL_4+2P-2.0-90D_ | SeeedOPL-Connector-2016:USB4+2-2.5-90D-15.8X12MM |  | T/H | 5 | 10 | UJ2-BH-W4-TH
1 | J1 | JACK-DC-005 | SeeedOPL-Connector-2016:JACK-DC-005 | OPL_Connector:DCJ3P-14.2X11.0X9.0MM |  | T/H | 5 |  | ADC-096-1
16 | C13, C14, C15, C32, C33, C50, C51, C68, C69, C74, C75, C76, C77, C78, C79, C80,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 | 0.1uF | Device:C | Capacitor_Tantalum_SMD:CP_EIA-1608-08_AVX-J |  | STOCK | 80
32 | D1, D2, D3, D4, D5, D6, D7, D8, D9, D10, D11, D12, D13, D14, D15, D16, D17, D18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 | BAV23A/Q | Device:D_Schottky_x2_ACom_KKA | SeeedOPL-Diode-2016:SOT-23 |  | <SHORT> | 160 | 180 | BAV23A,215
1 | D33 | SMD-LED-CLEAR-GREEN_0805_ | OPL_Optoelectronics:SMD-LED-CLEAR-GREEN_0805_ | Resistor_SMD:R_0805_2012Metric |  |  | 5 | 20 | 5975316507F
32 | Q1, Q2, Q3, Q4, Q13, Q14, Q15, Q16, Q25, Q26, Q27, Q28, Q37, Q38, Q39, Q40, Q49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 | 2N7002DW-7-F | CLRLibrary:6N7002 | Package_TO_SOT_SMD:SOT-363_SC-70-6_Handsoldering |  |  | 160 | 200 | 2N7002DW H6327
64 | Q5, Q6, Q7, Q8, Q9, Q10, Q11, Q12, Q17, Q18, Q19, Q20, Q21, Q22, Q23, Q24, Q29,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 | SMD-MOSFET-P-CH-VDC=30V-ID=4.3A-NCE3407A_SOT-23_ | SerialIOProc-rescue:SMD-MOSFET-P-CH-VDC=30V-ID=4.3A-NCE3407A_SOT-23_-OPL_Discre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 | OPL_Discrete_Semiconductor:SOT-23 |  |  | 320 | 400 | RM3407
1 | SD1 | MICRO-SD-CARD-SOCKET-9P_ST-TF-003A_ | OPL_Connector:MICRO-SD-CARD-SOCKET-9P_ST-TF-003A_ | OPL_Connector:MICRO-SD9+4P-SMD-16.1X14.5X1.85MM |  | Back Side | 5 | 5 | 105078-0001
8 | U2, U3, U4, U5, U6, U7, U8, U9 | 74HC597 | SerialIOProc-rescue:74HC595 | SMD_Packages:SO-16-N | 24 |  | 40 | 25 | 74hc597D,653
8 | U10, U11, U12, U13, U14, U15, U16, U17 | 74HC595D,118 | SerialIOProc-rescue:74HC595 | SMD_Packages:SO-16-N | 16 |  | 40 | 25 | 74HC595D,118
1 | U18 | AP1117-33 | Regulator_Linear:AP1117-33 | Package_TO_SOT_SMD:SOT-223-3_TabPin2 | 50 | STOCK | -45
16 | RN33,RN34,RN35,RN36,RN37,RN38,RN39,RN40,RN41,RN42,RN43,RN44,RN45,RN46,RN47,RN48 |  |  |  |  |  | 80 | 100 | 744C083103JPTR
16 | RN12,RN13,RN14,RN16,RN20,RN21,RN22,RN24,RN28,RN29,RN30,RN32,RN4,RN5,RN6,RN8 |  |  |  | 41 |  | 39 | 100 | 744C083331JP
16 | RN1,RN10,RN11,RN15,RN17,RN18,RN19,RN2,RN23,RN25,RN26,RN27,RN3,RN31,RN7,RN9 |  |  |  | 117 | STOCK | -37

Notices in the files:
Firmware/12or24Input_18F46Q10.X/mcc_generated_files/pin_manager.h:
(c) 2018 Microchip Technology Inc. and its subsidiaries.
Hardware/SAMdriver32 - RevB as built 190827/Peterson_SerialIO/SamDriver32.kicad_pcb:
SamDriver32 Rev B (c)2019 08 26
